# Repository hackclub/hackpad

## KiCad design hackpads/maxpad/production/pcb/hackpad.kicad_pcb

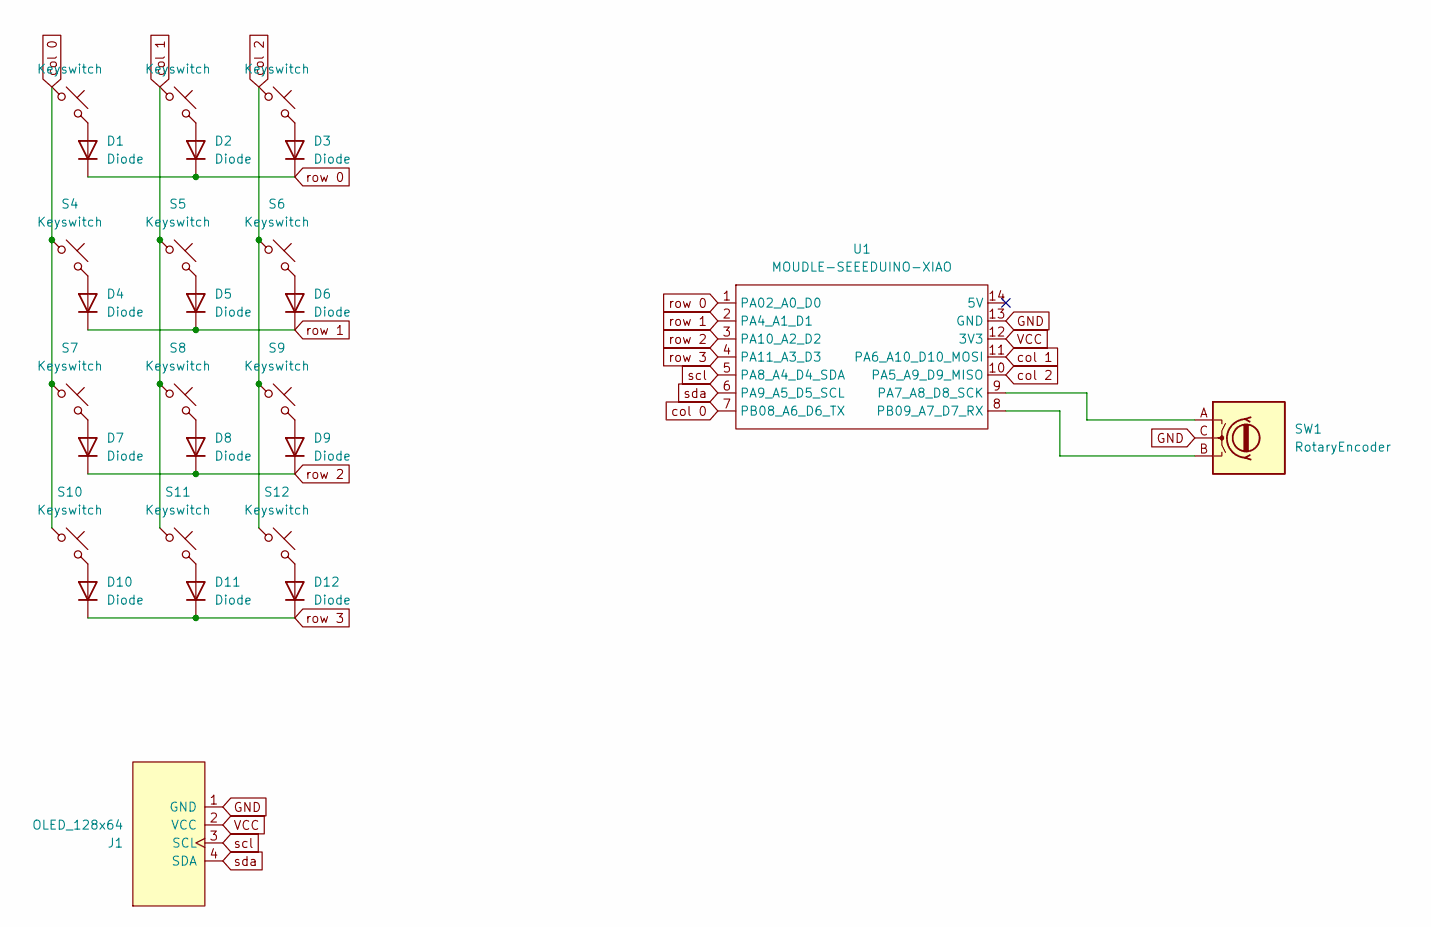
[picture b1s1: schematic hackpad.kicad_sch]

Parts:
D1, D2, D3, D4, D5, D6, D7, D8, D9, D10, D11, D12: Diode; Diode_DO-35
J1: OLED_128x64
S1, S2, S3, S4, S5, S6, S7, S8, S9, S10, S11, S12: Keyswitch; MX_PCB_1.00u
SW1: RotaryEncoder; RotaryEncoder_Alps_EC11E_Vertical_H20mm
U1: MOUDLE-SEEEDUINO-XIAO; MOUDLE14P-2.54-21X17.8MM

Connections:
GND: J1.1 (GND), SW1.C, U1.13 (GND)
unnamed: D1.2 (A), S1.2
unnamed: D2.2 (A), S2.2
unnamed: D3.2 (A), S3.2
unnamed: D4.2 (A), S4.2
unnamed: D5.2 (A), S5.2
unnamed: D6.2 (A), S6.2
unnamed: D7.2 (A), S7.2
unnamed: D8.2 (A), S8.2
unnamed: D9.2 (A), S9.2
unnamed: D10.2 (A), S10.2
unnamed: D11.2 (A), S11.2
unnamed: D12.2 (A), S12.2
unnamed: SW1.A, U1.9 (PA7_A8_D8_SCK)
unnamed: SW1.B, U1.8 (PB09_A7_D7_RX)
VCC: J1.2 (VCC), U1.12 (3V3)
col 0: S1.1, S4.1, S7.1, S10.1, U1.7 (PB08_A6_D6_TX)
col 1: S2.1, S5.1, S8.1, S11.1, U1.11 (PA6_A10_D10_MOSI)
col 2: S3.1, S6.1, S9.1, S12.1, U1.10 (PA5_A9_D9_MISO)
row 0: D1.1 (K), D2.1 (K), D3.1 (K), U1.1 (PA02_A0_D0)
row 1: D4.1 (K), D5.1 (K), D6.1 (K), U1.2 (PA4_A1_D1)
row 2: D7.1 (K), D8.1 (K), D9.1 (K), U1.3 (PA10_A2_D2)
row 3: D10.1 (K), D11.1 (K), D12.1 (K), U1.4 (PA11_A3_D3)
scl: J1.3 (SCL), U1.5 (PA8_A4_D4_SDA)
sda: J1.4 (SDA), U1.6 (PA9_A5_D5_SCL)

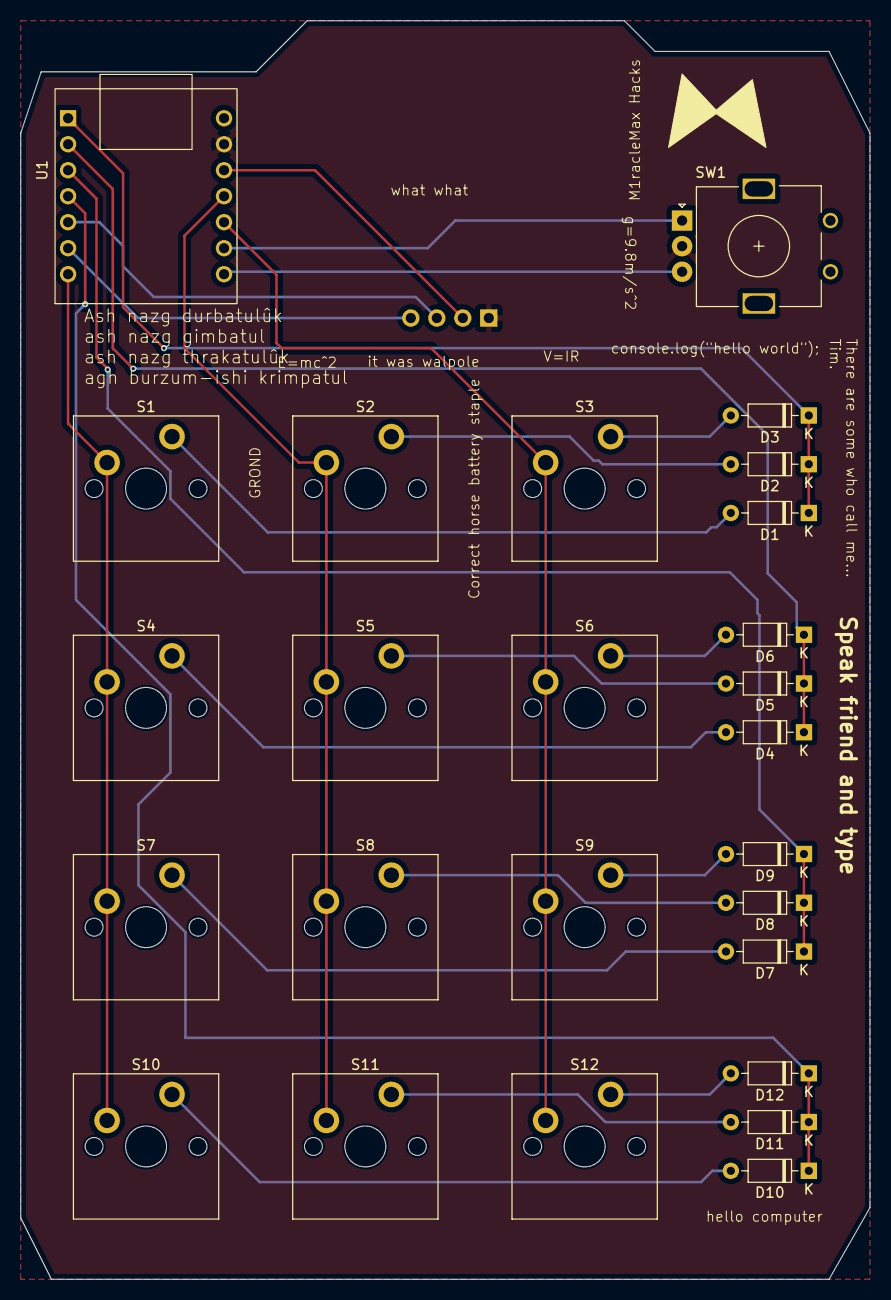
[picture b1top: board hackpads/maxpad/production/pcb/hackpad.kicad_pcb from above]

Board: 2 copper layers, 83.0 x 123.0 mm, 27 parts (0 on the bottom side), 25 nets.

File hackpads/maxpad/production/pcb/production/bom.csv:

Designator,Footprint,Quantity,Value,LCSC Part #
"D1, D10, D11, D12, D2, D3, D4, D5, D6, D7, D8, D9",Diode_DO-35,12,Diode,
J1,OLED_128x64,1,OLED_128x64,
"S1, S10, S11, S12, S2, S3, S4, S5, S6, S7, S8, S9",MX_PCB_1.00u,12,Keyswitch,
SW1,RotaryEncoder_Alps_EC11E_Vertical_H20mm,1,RotaryEncoder,
U1,MOUDLE14P-2.54-21X17.8MM,1,MOUDLE-SEEEDUINO-XIAO,

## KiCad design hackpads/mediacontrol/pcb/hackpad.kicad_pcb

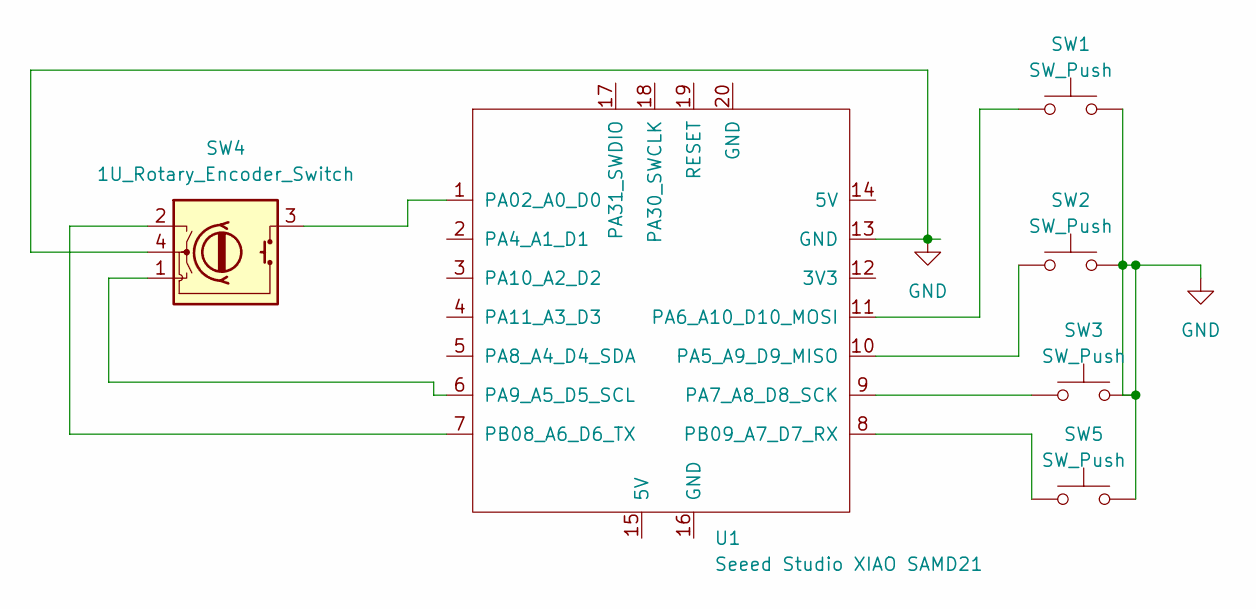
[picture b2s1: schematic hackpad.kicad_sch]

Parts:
SW1, SW2, SW3, SW5: SW_Push; SW_Cherry_MX_1.00u_PCB
SW4: 1U_Rotary_Encoder_Switch
U1: Seeed Studio XIAO SAMD21; XIAO-Generic-Thruhole-14P-2.54-21X17.8MM

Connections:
GND: SW1.2, SW2.2, SW3.2, SW4.4 (C), SW5.2, U1.13 (GND)
unnamed: SW4.2 (A), U1.7 (PB08_A6_D6_TX)
unnamed: SW4.1 (B), U1.6 (PA9_A5_D5_SCL)
unnamed: SW4.3 (E), U1.1 (PA02_A0_D0)
unnamed: SW2.1, U1.10 (PA5_A9_D9_MISO)
unnamed: SW1.1, U1.11 (PA6_A10_D10_MOSI)
unnamed: SW3.1, U1.9 (PA7_A8_D8_SCK)
unnamed: SW5.1, U1.8 (PB09_A7_D7_RX)

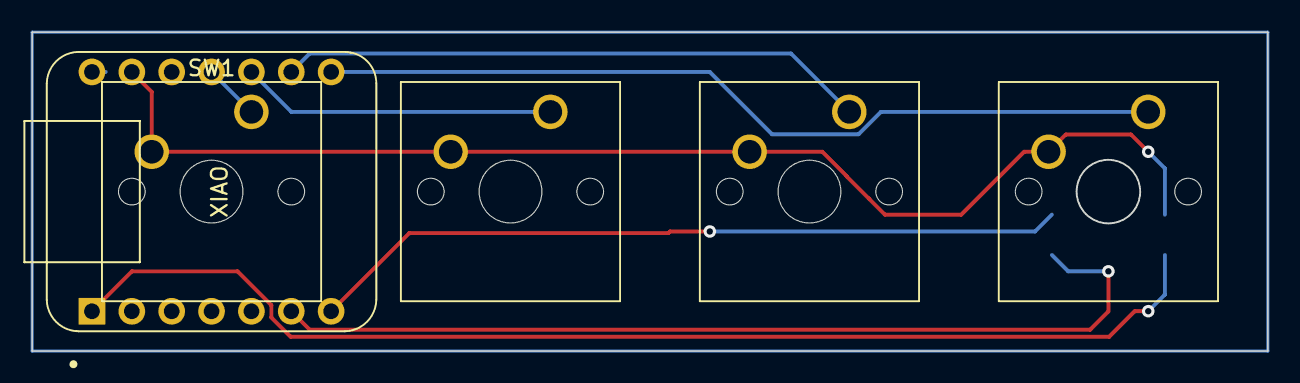
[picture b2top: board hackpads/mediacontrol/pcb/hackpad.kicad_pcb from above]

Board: 2 copper layers, 78.7 x 20.3 mm, 6 parts (1 on the bottom side), 8 nets.

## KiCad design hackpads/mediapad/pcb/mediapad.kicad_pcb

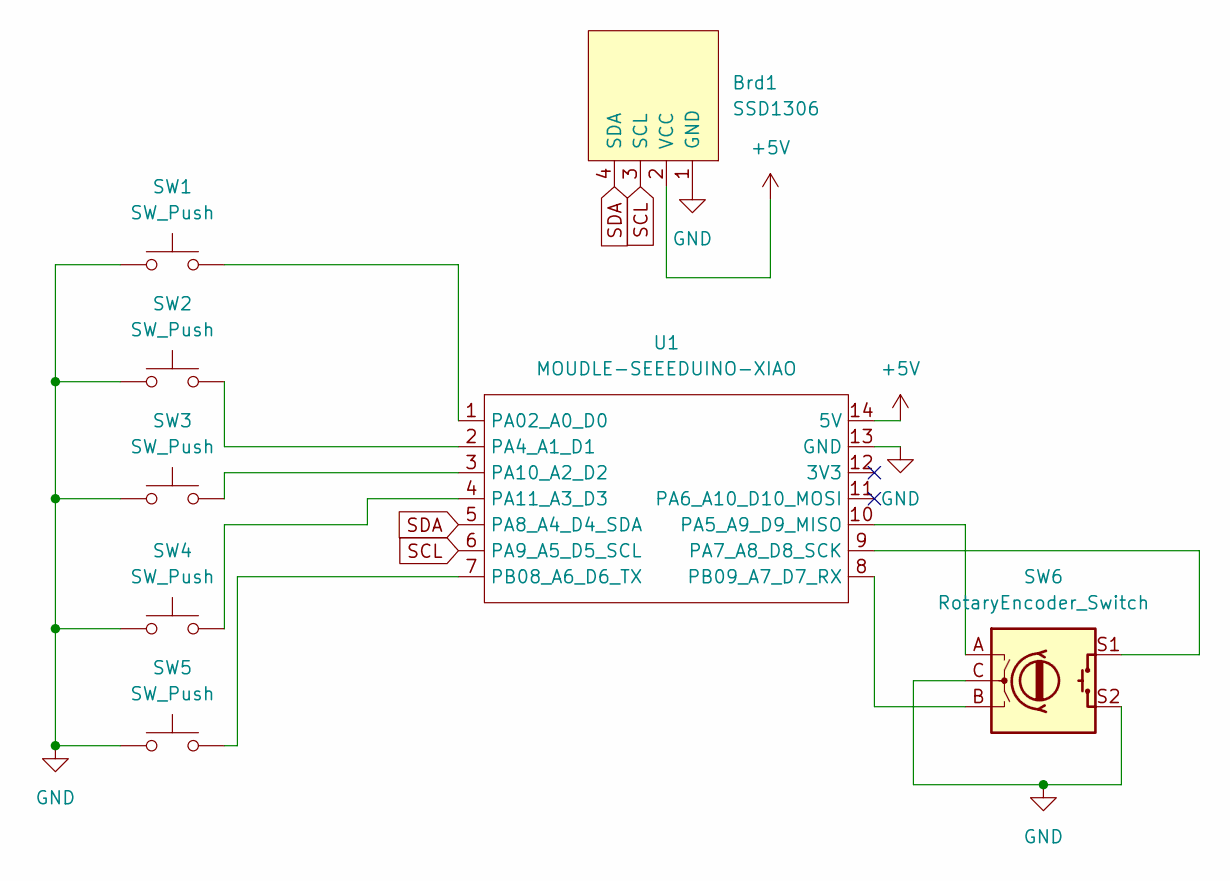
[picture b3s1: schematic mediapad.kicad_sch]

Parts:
Brd1: SSD1306; 128x64OLED
SW1, SW2, SW3, SW4, SW5: SW_Push; SW_Cherry_MX_1.00u_PCB
SW6: RotaryEncoder_Switch; RotaryEncoder_Alps_EC11E-Switch_Vertical_H20mm
U1: MOUDLE-SEEEDUINO-XIAO; XIAO-Generic-Hybrid-14P-2.54-21X17.8MM

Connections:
+5V: Brd1.2 (VCC), U1.14 (5V)
GND: Brd1.1 (GND), SW1.1, SW2.1, SW3.1, SW4.1, SW5.1, SW6.C, SW6.S2, U1.13 (GND)
unnamed: SW1.2, U1.1 (PA02_A0_D0)
unnamed: SW2.2, U1.2 (PA4_A1_D1)
unnamed: SW6.A, U1.10 (PA5_A9_D9_MISO)
unnamed: SW6.S1, U1.9 (PA7_A8_D8_SCK)
unnamed: SW3.2, U1.3 (PA10_A2_D2)
unnamed: SW4.2, U1.4 (PA11_A3_D3)
unnamed: SW5.2, U1.7 (PB08_A6_D6_TX)
unnamed: SW6.B, U1.8 (PB09_A7_D7_RX)
SCL: Brd1.3 (SCL), U1.6 (PA9_A5_D5_SCL)
SDA: Brd1.4 (SDA), U1.5 (PA8_A4_D4_SDA)

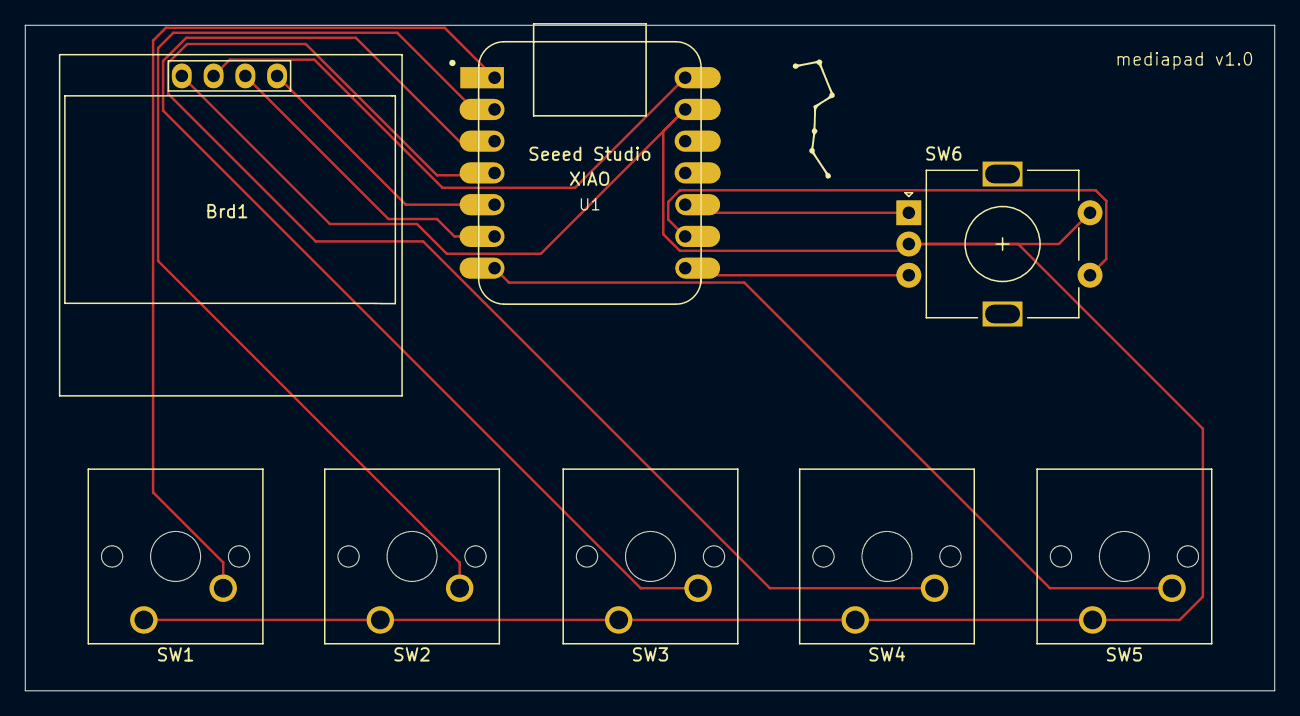
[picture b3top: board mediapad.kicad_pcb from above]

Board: 2 copper layers, 100.0 x 53.2 mm, 8 parts (0 on the bottom side), 12 nets.

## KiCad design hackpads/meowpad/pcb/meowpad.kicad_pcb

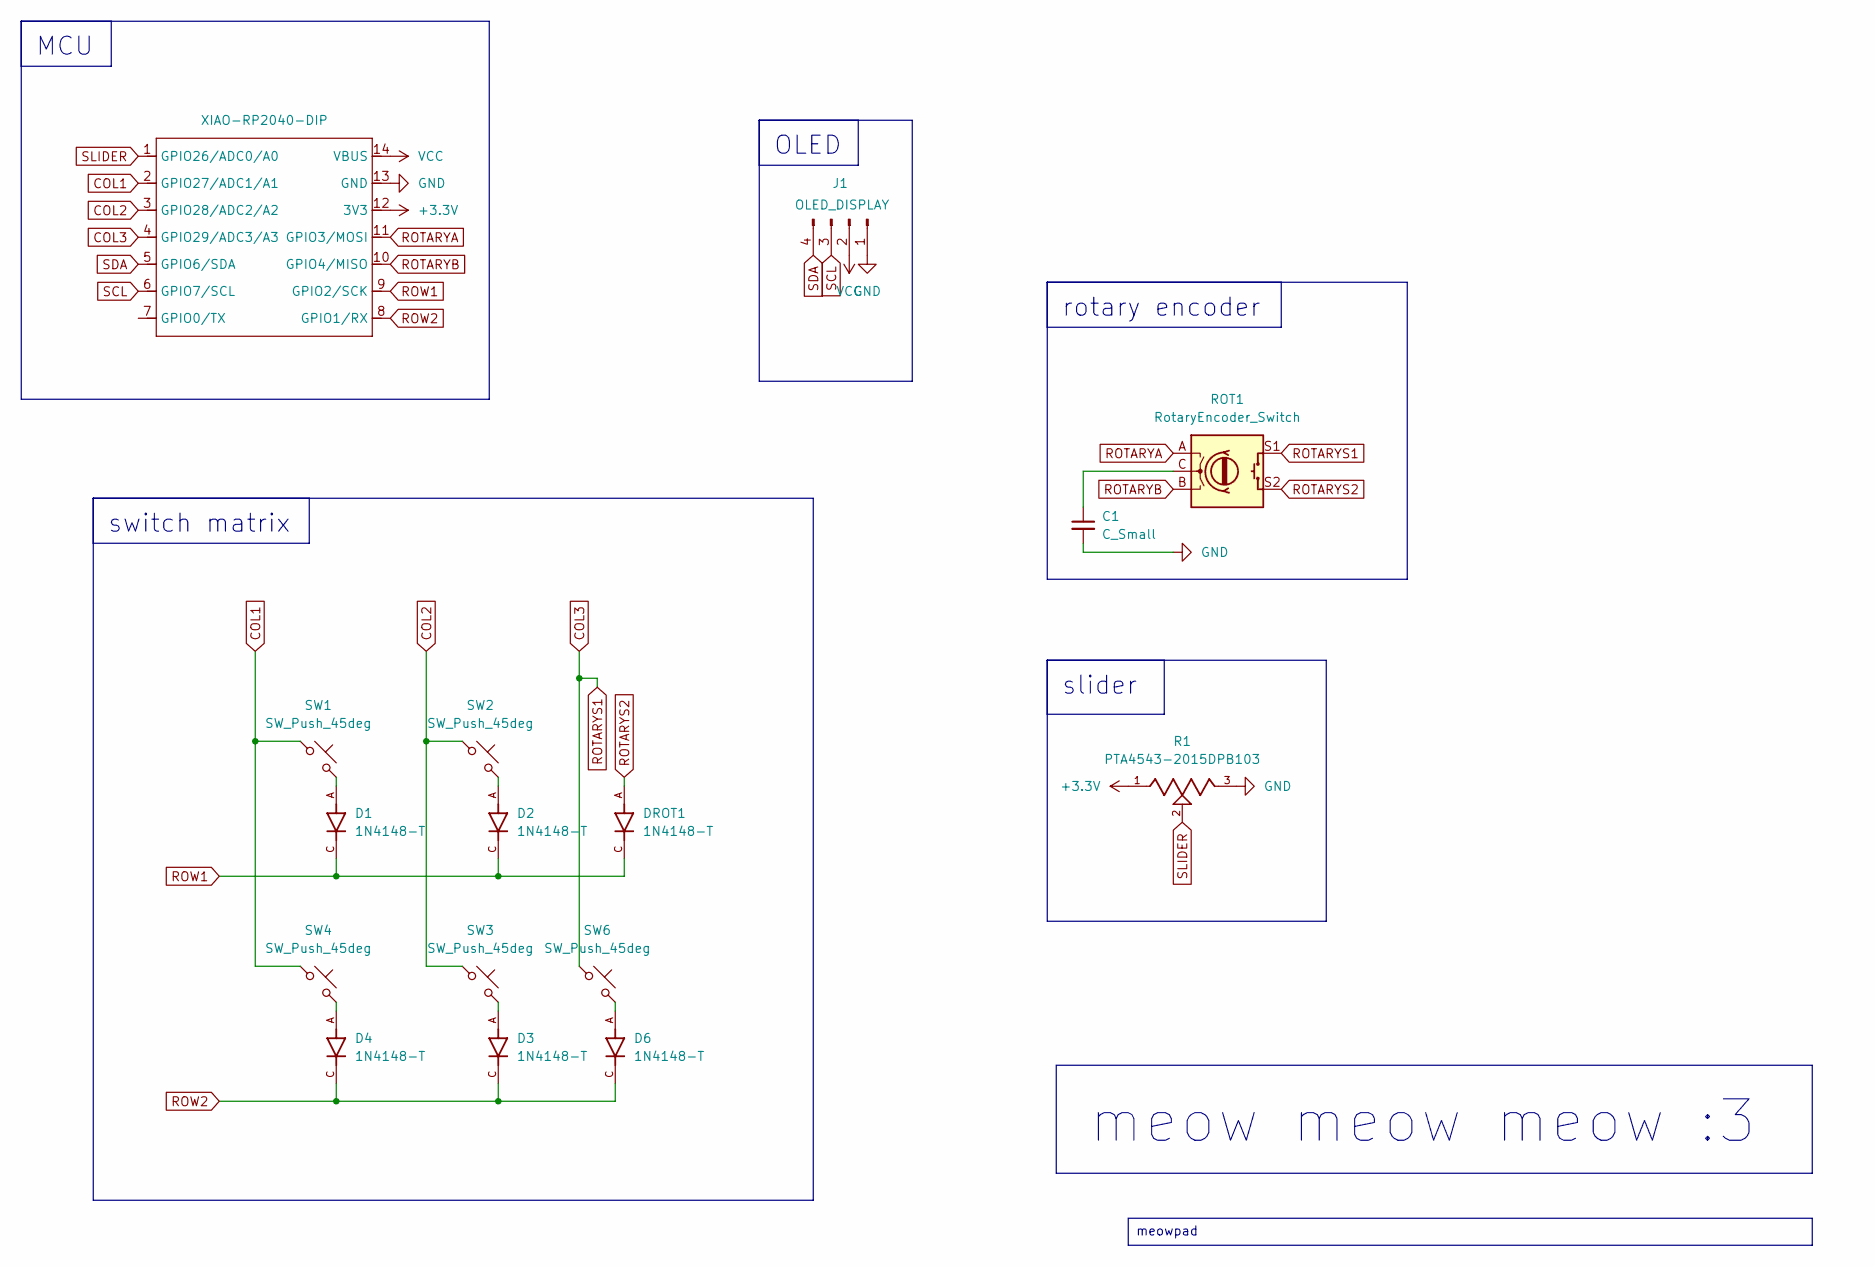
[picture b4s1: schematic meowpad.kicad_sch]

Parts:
C1: C_Small; CP_Radial_D5.0mm_P2.50mm
D1, D2, D3, D4, D6: 1N4148-T; DIOAD820W60L400D200; PARTREV 9-3
DROT1: 1N4148-T; DIOAD820W60L400D200; PARTREV 9-3
J1: OLED_DISPLAY; SSD1306-0.91-OLED-4pin-128x32
R1: PTA4543-2015DPB103; TRIM_PTA4543-2015DPB103; PARTREV 04/21
ROT1: RotaryEncoder_Switch; RotaryEncoder_Alps_EC11E-Switch_Vertical_H20mm_MountingHoles
SW1, SW2, SW3, SW4, SW6: SW_Push_45deg; SW_Cherry_MX_1.00u_PCB
U2: XIAO-RP2040-DIP

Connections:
+3.3V: R1.1, U2.12 (3V3)
COL1: SW1.1, SW4.1, U2.2 (GPIO27/ADC1/A1)
COL2: SW2.1, SW3.1, U2.3 (GPIO28/ADC2/A2)
COL3: ROT1.S1, SW6.1, U2.4 (GPIO29/ADC3/A3)
GND: C1.2, J1.1, R1.3, U2.13 (GND)
unnamed: C1.1, ROT1.C
unnamed: D1.A, SW1.2
unnamed: D2.A, SW2.2
unnamed: D3.A, SW3.2
unnamed: D4.A, SW4.2
unnamed: D6.A, SW6.2
ROTARYA: ROT1.A, U2.11 (GPIO3/MOSI)
ROTARYB: ROT1.B, U2.10 (GPIO4/MISO)
ROTARYS2: DROT1.A, ROT1.S2
ROW1: D1.C, D2.C, DROT1.C, U2.9 (GPIO2/SCK)
ROW2: D3.C, D4.C, D6.C, U2.8 (GPIO1/RX)
SCL: J1.3, U2.6 (GPIO7/SCL)
SDA: J1.4, U2.5 (GPIO6/SDA)
SLIDER: R1.2, U2.1 (GPIO26/ADC0/A0)
VCC: J1.2, U2.14 (VBUS)

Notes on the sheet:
meowpad
rotary encoder
meow meow meow :3
switch matrix
MCU
slider
OLED

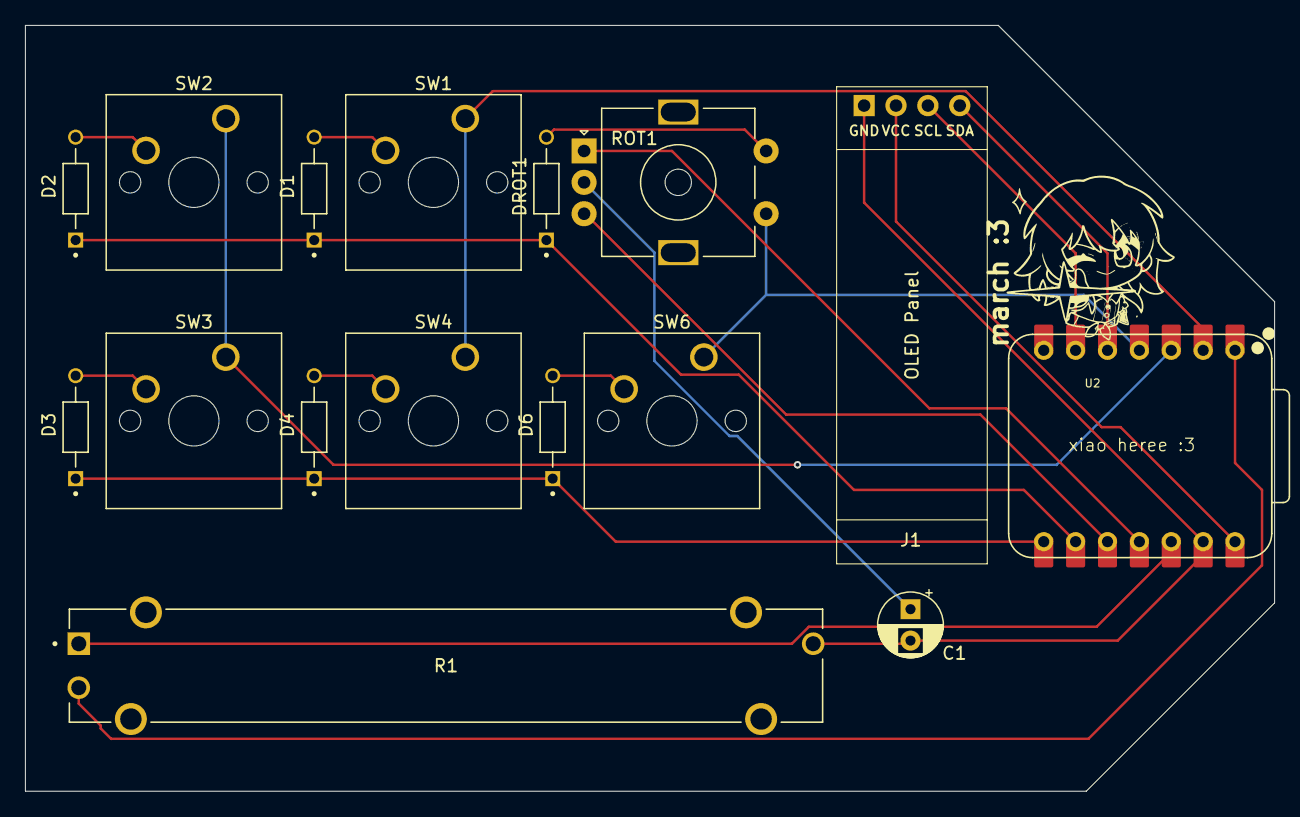
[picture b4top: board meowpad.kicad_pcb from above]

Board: 2 copper layers, 99.5 x 61.0 mm, 18 parts (1 on the bottom side), 20 nets.

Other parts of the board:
NYA: LOGO; catgirl
march :3: LOGO; march

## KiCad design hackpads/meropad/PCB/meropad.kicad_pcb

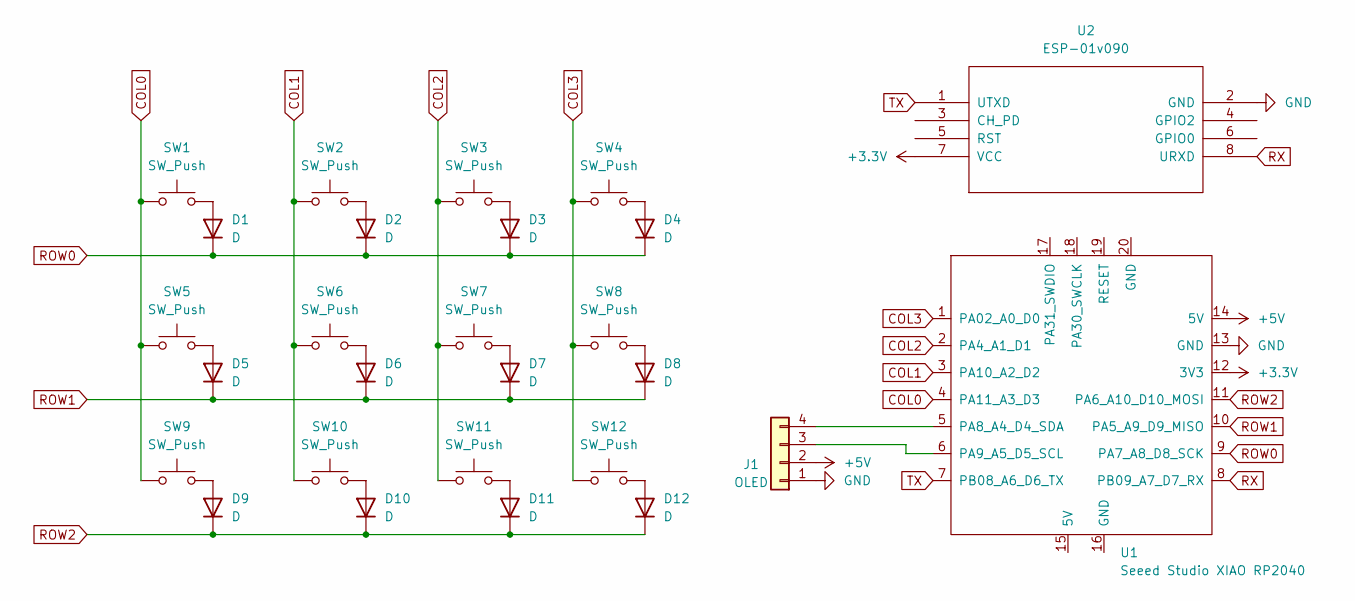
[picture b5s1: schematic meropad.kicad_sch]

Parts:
D1, D2, D3, D4, D5, D6, D7, D8, D9, D10, D11, D12: D; D_DO-35_SOD27_P7.62mm_Horizontal
J1: OLED; SSD1306-0.91-OLED-4pin-128x32
SW1, SW2, SW3, SW4, SW5, SW6, SW7, SW8, SW9, SW10, SW11, SW12: SW_Push; SW_Cherry_MX_1.00u_PCB
U1: Seeed Studio XIAO RP2040; XIAO-Generic-Thruhole-14P-2.54-21X17.8MM
U2: ESP-01v090; ESP-01

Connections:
+3.3V: U1.12 (3V3), U2.7 (VCC)
+5V: J1.2, U1.14 (5V)
COL0: SW1.1, SW5.1, SW9.1, U1.4 (PA11_A3_D3)
COL1: SW2.1, SW6.1, SW10.1, U1.3 (PA10_A2_D2)
COL2: SW3.1, SW7.1, SW11.1, U1.2 (PA4_A1_D1)
COL3: SW4.1, SW8.1, SW12.1, U1.1 (PA02_A0_D0)
GND: J1.1, U1.13 (GND), U2.2 (GND)
unnamed: D1.2 (A), SW1.2
unnamed: D2.2 (A), SW2.2
unnamed: D3.2 (A), SW3.2
unnamed: D4.2 (A), SW4.2
unnamed: D5.2 (A), SW5.2
unnamed: D6.2 (A), SW6.2
unnamed: D7.2 (A), SW7.2
unnamed: D8.2 (A), SW8.2
unnamed: D9.2 (A), SW9.2
unnamed: D10.2 (A), SW10.2
unnamed: D11.2 (A), SW11.2
unnamed: D12.2 (A), SW12.2
unnamed: J1.3, U1.6 (PA9_A5_D5_SCL)
unnamed: J1.4, U1.5 (PA8_A4_D4_SDA)
ROW0: D1.1 (K), D2.1 (K), D3.1 (K), D4.1 (K), U1.9 (PA7_A8_D8_SCK)
ROW1: D5.1 (K), D6.1 (K), D7.1 (K), D8.1 (K), U1.10 (PA5_A9_D9_MISO)
ROW2: D9.1 (K), D10.1 (K), D11.1 (K), D12.1 (K), U1.11 (PA6_A10_D10_MOSI)
RX: U1.8 (PB09_A7_D7_RX), U2.8 (URXD)
TX: U1.7 (PB08_A6_D6_TX), U2.1 (UTXD)

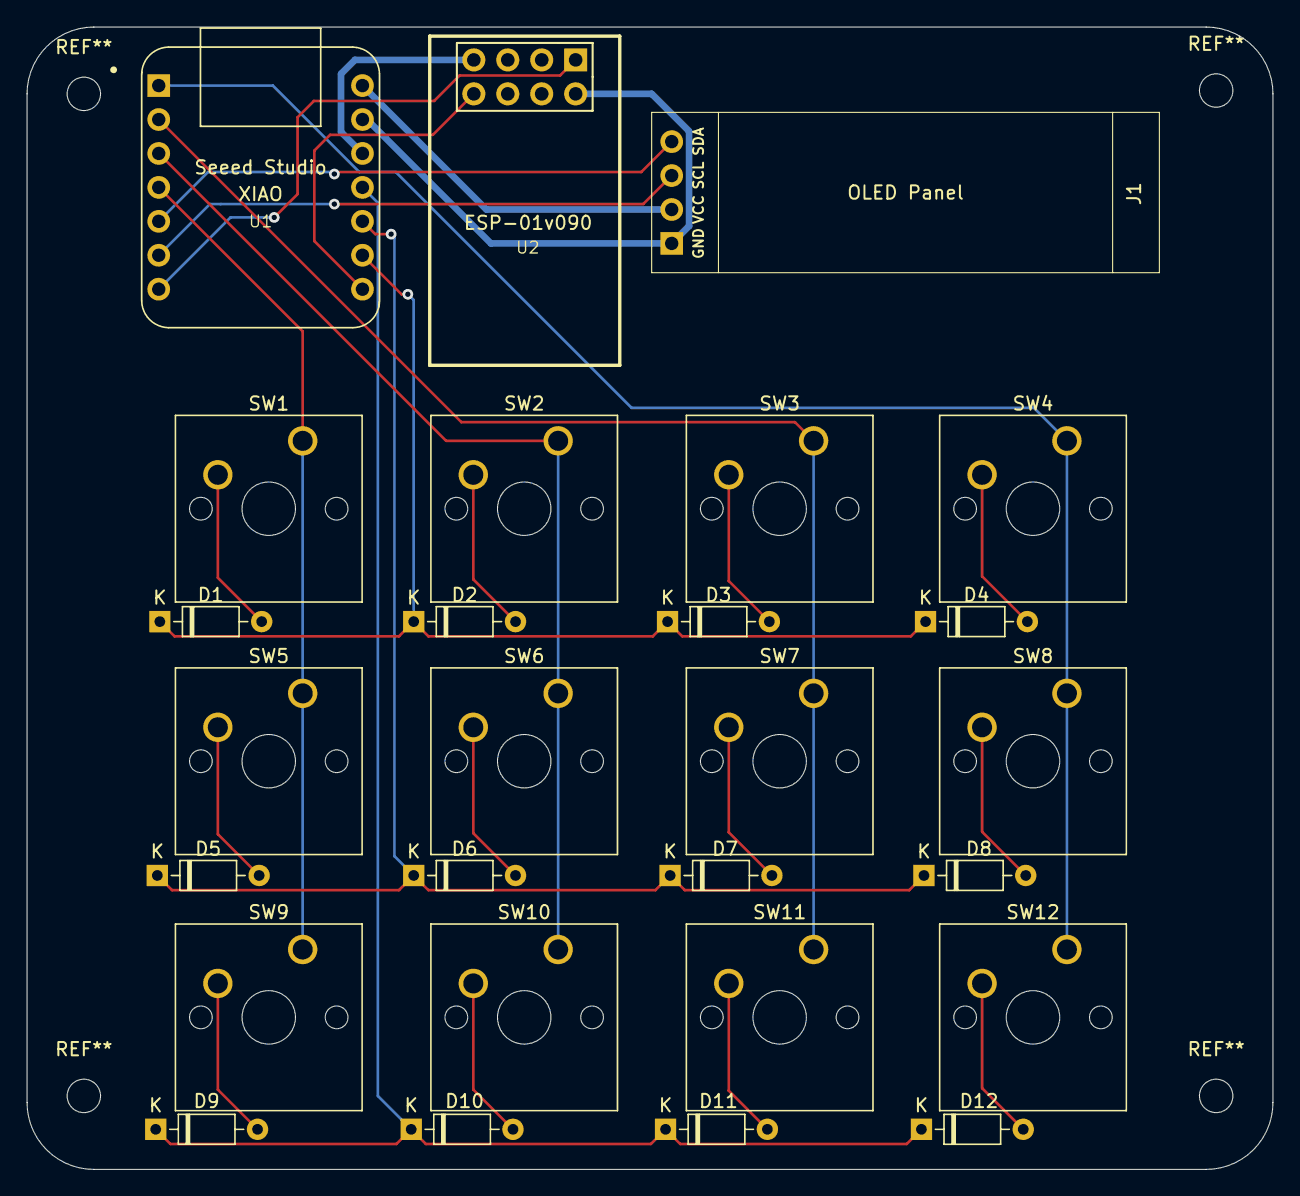
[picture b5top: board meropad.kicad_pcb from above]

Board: 2 copper layers, 93.2 x 85.5 mm, 27 parts (0 on the bottom side), 26 nets.

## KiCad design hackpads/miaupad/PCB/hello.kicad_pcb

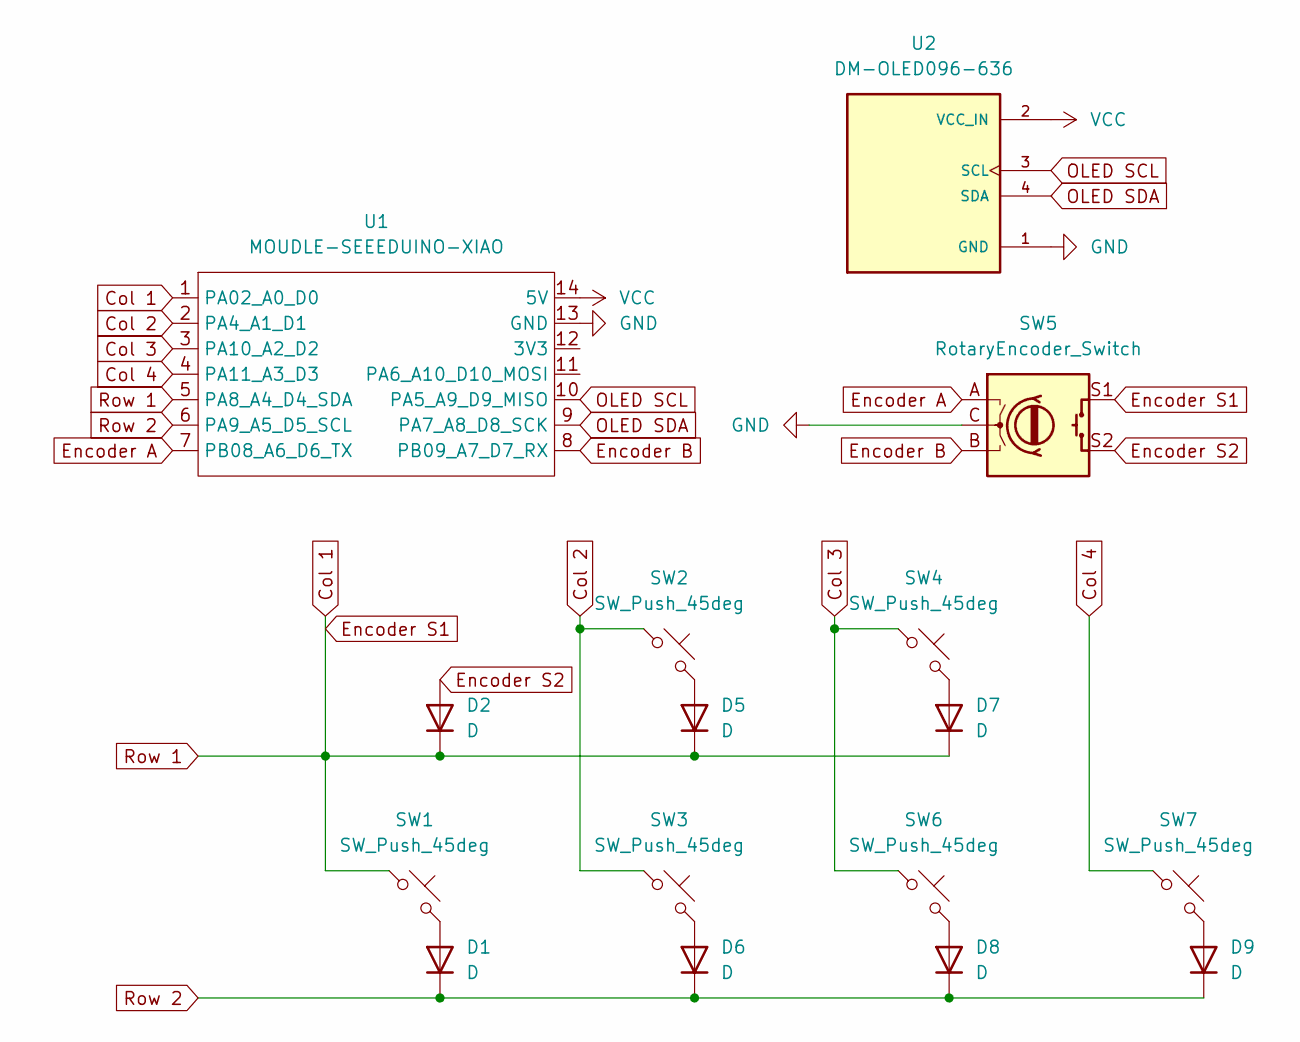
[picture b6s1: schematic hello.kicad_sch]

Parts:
D1, D2, D5, D6, D7, D8, D9: D; Diode_DO-35
SW1, SW2, SW3, SW4, SW6, SW7: SW_Push_45deg; 1U-Switch
SW5: RotaryEncoder_Switch; RotaryEncoder_Alps_EC11E-Switch_Vertical_H20mm
U1: MOUDLE-SEEEDUINO-XIAO; XIAO
U2: DM-OLED096-636; SSD1306-0.91-OLED-4pin-128x32; PARTREV 2018-09-10

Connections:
Col 1: D2.1 (K), D5.1 (K), D7.1 (K), SW1.1, SW5.S1, U1.1 (PA02_A0_D0), U1.5 (PA8_A4_D4_SDA)
Col 2: SW2.1, SW3.1, U1.2 (PA4_A1_D1)
Col 3: SW4.1, SW6.1, U1.3 (PA10_A2_D2)
Col 4: SW7.1, U1.4 (PA11_A3_D3)
Encoder A: SW5.A, U1.7 (PB08_A6_D6_TX)
Encoder B: SW5.B, U1.8 (PB09_A7_D7_RX)
Encoder S2: D2.2 (A), SW5.S2
GND: SW5.C, U1.13 (GND), U2.1 (GND)
unnamed: D1.2 (A), SW1.2
unnamed: D5.2 (A), SW2.2
unnamed: D6.2 (A), SW3.2
unnamed: D7.2 (A), SW4.2
unnamed: D8.2 (A), SW6.2
unnamed: D9.2 (A), SW7.2
OLED SCL: U1.10 (PA5_A9_D9_MISO), U2.3 (SCL)
OLED SDA: U1.9 (PA7_A8_D8_SCK), U2.4 (SDA)
Row 2: D1.1 (K), D6.1 (K), D8.1 (K), D9.1 (K), U1.6 (PA9_A5_D5_SCL)
VCC: U1.14 (5V), U2.2 (VCC_IN)

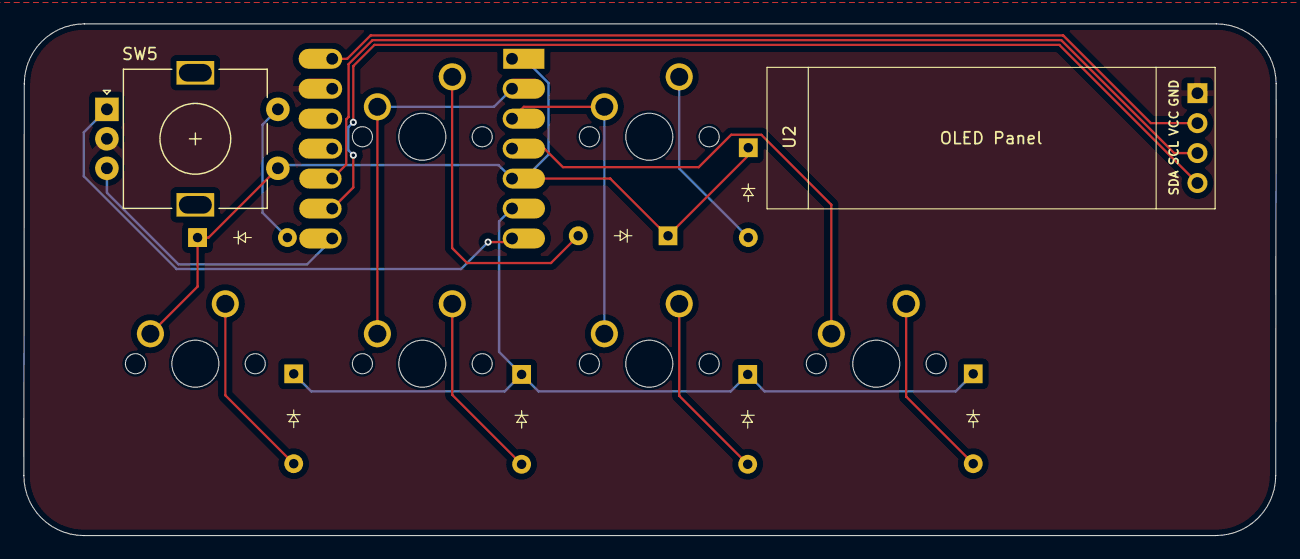
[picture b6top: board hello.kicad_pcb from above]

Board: 2 copper layers, 106.2 x 43.4 mm, 16 parts (1 on the bottom side), 18 nets.

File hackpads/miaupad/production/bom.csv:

Designator,Footprint,Quantity,Value,LCSC Part #
"D1, D2, D5, D6, D7, D8, D9",Diode_DO-35,7,D,
"SW1, SW2, SW3, SW4, SW6, SW7",1U-Switch,6,SW_Push_45deg,
SW5,RotaryEncoder_Alps_EC11E-Switch_Vertical_H20mm,1,RotaryEncoder_Switch,
U1,XIAO,1,MOUDLE-SEEEDUINO-XIAO,
U2,SSD1306-0.91-OLED-4pin-128x32,1,DM-OLED096-636,

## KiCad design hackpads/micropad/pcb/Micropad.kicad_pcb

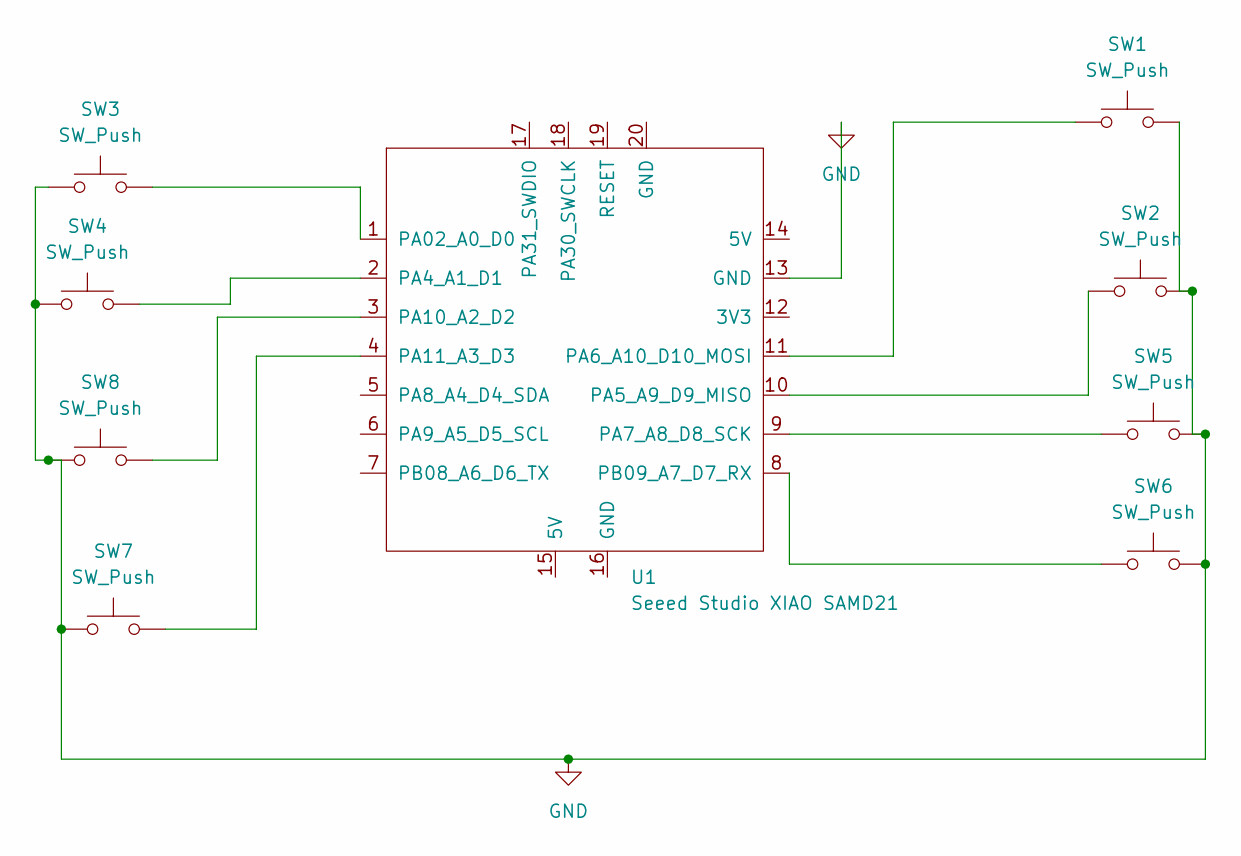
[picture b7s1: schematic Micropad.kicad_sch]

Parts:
SW1, SW2, SW3, SW4, SW5, SW6, SW7, SW8: SW_Push; SW_Cherry_MX_1.00u_PCB
U1: Seeed Studio XIAO SAMD21; XIAO-Generic-Hybrid-14P-2.54-21X17.8MM

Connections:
GND: SW1.2, SW2.2, SW3.1, SW4.1, SW5.2, SW6.2, SW7.1, SW8.1, U1.13 (GND)
unnamed: SW3.2, U1.1 (PA02_A0_D0)
unnamed: SW4.2, U1.2 (PA4_A1_D1)
unnamed: SW2.1, U1.10 (PA5_A9_D9_MISO)
unnamed: SW1.1, U1.11 (PA6_A10_D10_MOSI)
unnamed: SW5.1, U1.9 (PA7_A8_D8_SCK)
unnamed: SW8.2, U1.3 (PA10_A2_D2)
unnamed: SW7.2, U1.4 (PA11_A3_D3)
unnamed: SW6.1, U1.8 (PB09_A7_D7_RX)

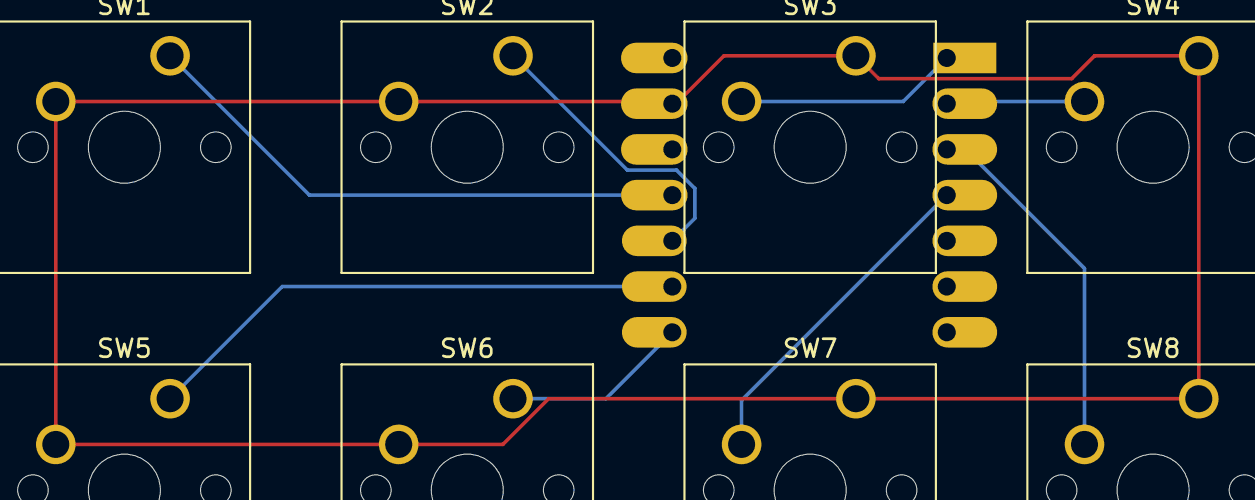
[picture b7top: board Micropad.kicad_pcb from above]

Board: 2 copper layers, 9 parts (1 on the bottom side), 9 nets.
